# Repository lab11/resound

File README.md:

Resound
==============

This is intended to be a high power version of the 
[Ekho Project](http://github.com/jhester/ekho) to be
used with larger solar powered sensor deployments.

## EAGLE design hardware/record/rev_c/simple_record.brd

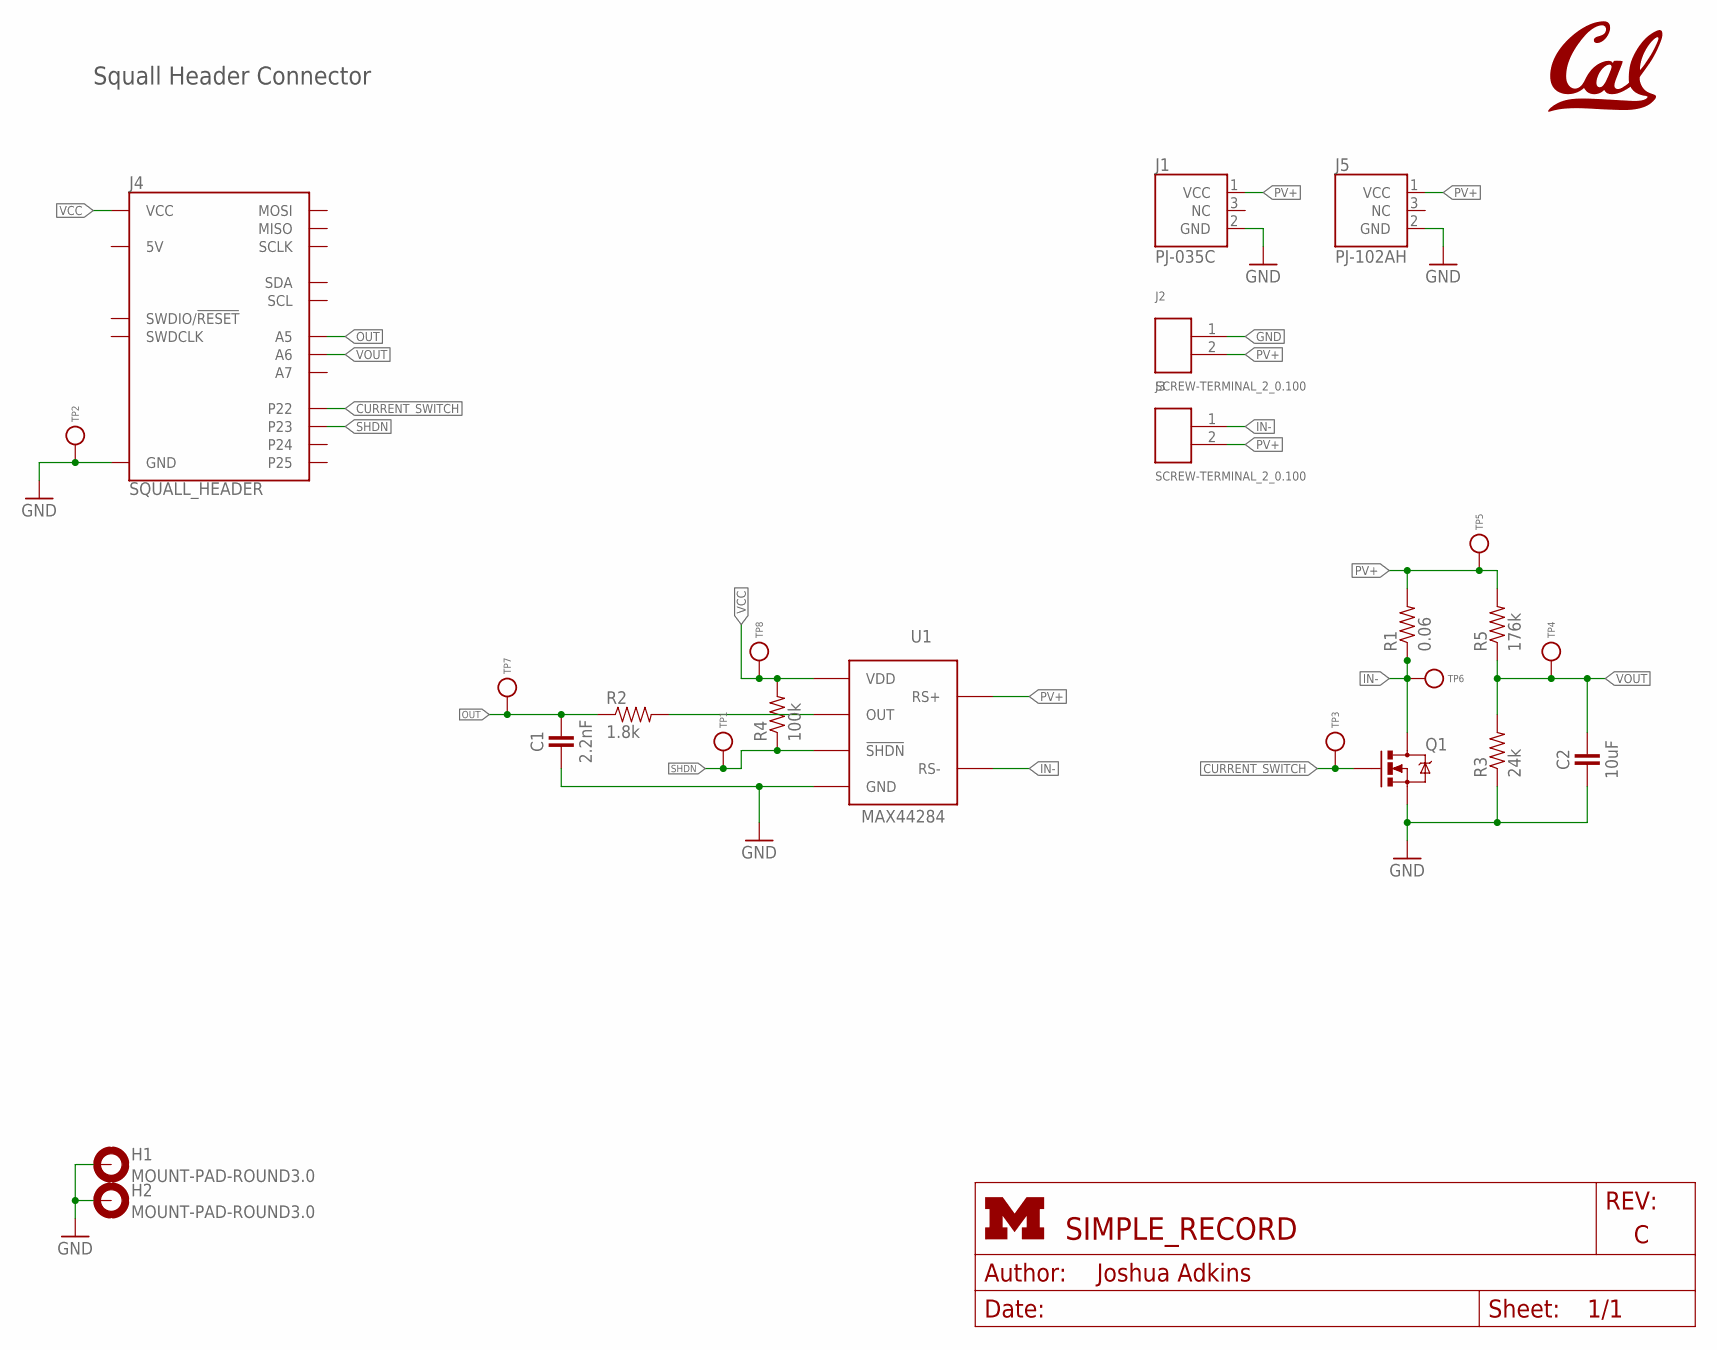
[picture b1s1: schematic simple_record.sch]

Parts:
C1: 2.2nF; 0402_CAP
C2: 10uF; 0603_CAP
H1, H2: MOUNT-PAD-ROUND3.0; 3,0-PAD
J1: PJ-035C
J2, J3: SCREW-TERMINAL_2_0.100; CONN_BLOCK_2
J4: SQUALL_HEADER
J5: PJ-102AH
Q1: MOSFET-NCHANNELSMD; SOT23-3; DIGIKEY DMN3023L-7DICT-ND
R1: 0.06; 0603-RES
R2: 1.8k; 0603-RES
R3: 24k; 0603-RES
R4: 100k; 0603-RES
R5: 176k; 0603-RES
TP1, TP2, TP3, TP4, TP5, TP6, TP7, TP8: TEST_POINT_0.040IN; TESTPOINT_0.040IN
U1: MAX44284; SOT-23-6
U$1: UCB_CAL75MIL; UCB_CAL_75MIL

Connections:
CURRENT_SWITCH: J4.A2 (P22), Q1.1 (G), TP3.TESTPOINT
GND: C1.2, C2.2, H1.B3,0, H2.B3,0, J1.2 (GND), J2.1, J4.A9 (GND), J4.A10 (GND), J5.2 (GND), Q1.2 (S), R3.1, TP2.TESTPOINT, U1.2 (GND)
IN-: J3.1, Q1.3 (D), R1.1, TP6.TESTPOINT, U1.4 (RS-)
unnamed: R2.2, U1.5 (OUT)
OUT: C1.1, J4.B9 (A5), R2.1, TP7.TESTPOINT
PV+: J1.1 (VCC), J2.2, J3.2, J5.1 (VCC), R1.2, R5.2, TP5.TESTPOINT, U1.3 (RS+)
SHDN: J4.A4 (P23), R4.1, TP1.TESTPOINT, U1.6 (!SHDN)
VCC: J4.A1 (VCC), J4.A3 (VCC), R4.2, TP8.TESTPOINT, U1.1 (VDD)
VOUT: C2.1, J4.B7 (A6), R3.2, R5.1, TP4.TESTPOINT

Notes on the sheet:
Squall Header Connector

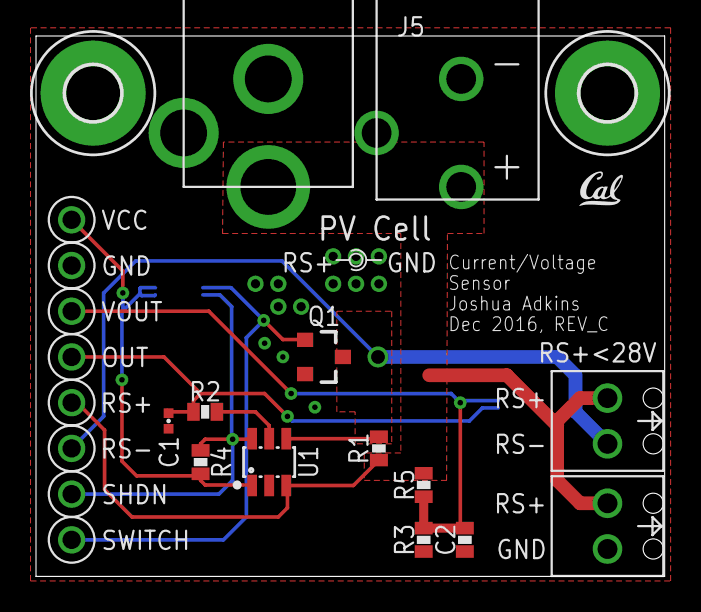
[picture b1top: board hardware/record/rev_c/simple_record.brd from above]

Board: 2 copper layers, 34.9 x 30.0 mm, 25 parts (0 on the bottom side), 9 nets.

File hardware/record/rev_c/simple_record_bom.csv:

# Bill of Materials
# Converted from simple_record_bom.xlsx
# Generated by bom_to_text.py

Qty,Value,Device,Package,Parts,Description,DIGIKEY,MOUSER,NEWARK
1,2.2nF,CAPACITOR,0402_CAP,C1,0402 Capacitor,587-1059-1-ND,,
1,10uF,CAPACITOR0603_CAP,0603_CAP,C2,0603 Capacitor,490-3298-1-ND,,
1,PJ-035C,PJ-035C,PJ-035C,J1,A 1/3.4mm barrel jack part,CP-035C-ND,,
2,SCREW-TERMINAL_2_0.100,SCREW-TERMINAL_2_0.100,CONN_BLOCK_2,"J2, J3",2x 0.100 in screw terminal block,277-1273-ND,651-1725656,71C4107
2,SQUALL_HEADER,SQUALL_HEADER,SQUALL_HEADER,"J4A, J4B",Header for a sensor board on top of the Squall BLE tag board.,H11617CT-ND,,
1,PJ-102AH,PJ-102AH,PJ-102AH,J5,DC Power Jack,CP-102AH-ND,,
1,MOSFET-NCHANNELSMD,MOSFET-NCHANNELSMD,SOT23-3,Q1,Generic NMOS footprint,DMN3023L-7DICT-ND,,
1,0.06,RESISTOR,0603-RES,R1,Resistor,WSLPA-.06CT-ND,,
1,1.8k,RESISTOR,0603-RES,R2,Resistor,311-1.8KGRCT-ND,,
1,24k,RESISTOR,0603-RES,R3,Resistor,RHM24KCFCT-ND,,
1,100k,RESISTOR,0603-RES,R4,Resistor,311-100KGRCT-ND,,
1,176k,RESISTOR,0603-RES,R5,Resistor,311-2094-1-ND,,
7,TEST_POINT_0.040IN,TEST_POINT_0.040IN,TESTPOINT_0.040IN,"TP1, TP2, TP3, TP4, TP5, TP6, TP7",0.040in Test Point,5001K-ND,,
1,MAX44284F,MAX44284F,SOT23-6,U1,,MAX44284FAUT+TCT-ND,,

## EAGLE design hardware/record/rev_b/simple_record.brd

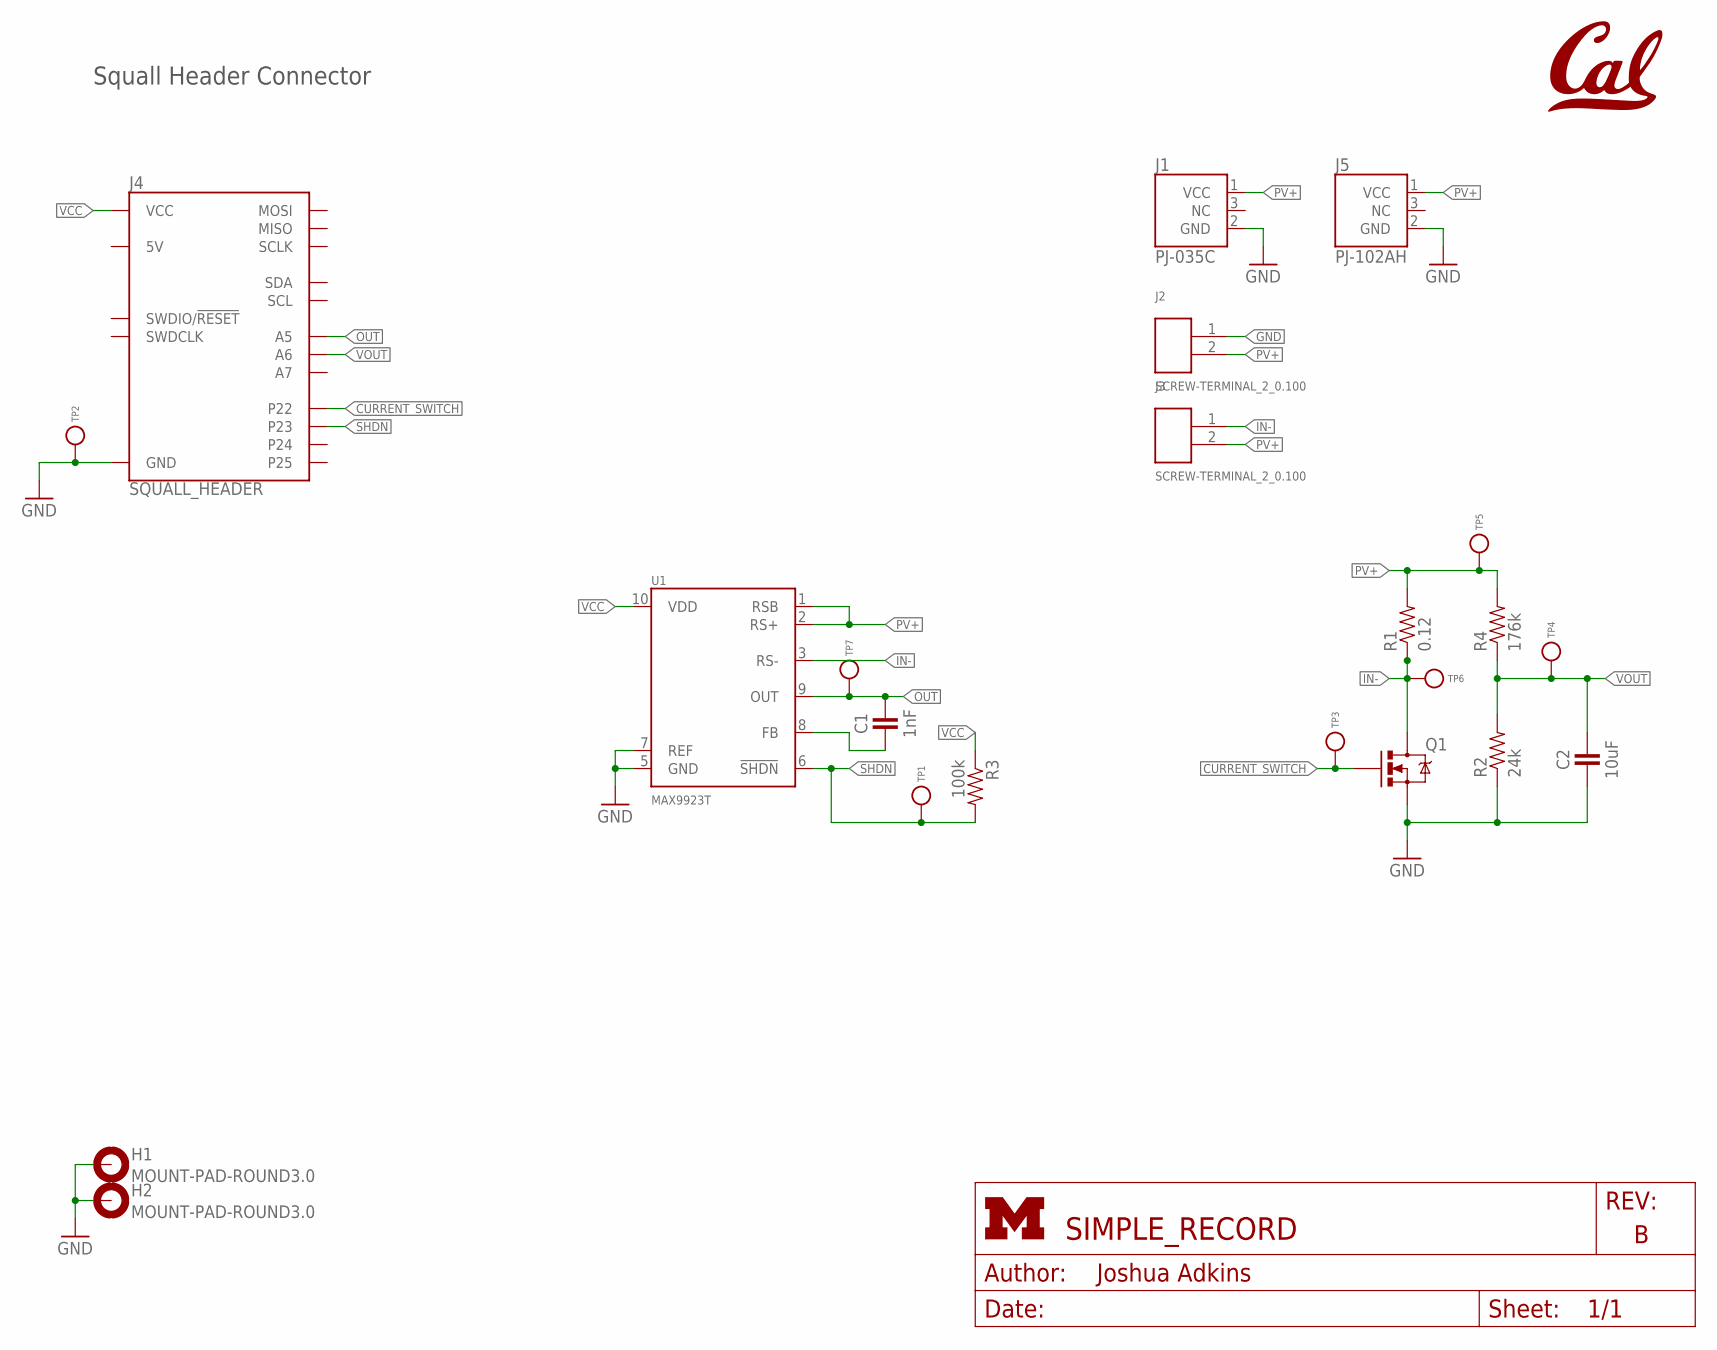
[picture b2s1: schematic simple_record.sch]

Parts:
C1: 1nF; 0402_CAP
C2: 10uF; 0603_CAP
H1, H2: MOUNT-PAD-ROUND3.0; 3,0-PAD
J1: PJ-035C
J2, J3: SCREW-TERMINAL_2_0.100; CONN_BLOCK_2
J4: SQUALL_HEADER
J5: PJ-102AH
Q1: MOSFET-NCHANNELSMD; SOT23-3; DIGIKEY DMN3023L-7DICT-ND
R1: 0.12; 0603-RES
R2: 24k; 0603-RES
R3: 100k; 0603-RES
R4: 176k; 0603-RES
TP1, TP2, TP3, TP4, TP5, TP6, TP7: TEST_POINT_0.040IN; TESTPOINT_0.040IN
U1: MAX9923T; UMAX10; DIGIKEY MAX9923TEUB+TCT-ND
U$1: UCB_CAL75MIL; UCB_CAL_75MIL

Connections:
CURRENT_SWITCH: J4.A2 (P22), Q1.1 (G), TP3.TESTPOINT
GND: C2.2, H1.B3,0, H2.B3,0, J1.2 (GND), J2.1, J4.A9 (GND), J4.A10 (GND), J5.2 (GND), Q1.2 (S), R2.1, TP2.TESTPOINT, U1.5 (GND), U1.7 (REF)
IN-: J3.1, Q1.3 (D), R1.1, TP6.TESTPOINT, U1.3 (RS-)
unnamed: C1.2, U1.8 (FB)
OUT: C1.1, J4.B9 (A5), TP7.TESTPOINT, U1.9 (OUT)
PV+: J1.1 (VCC), J2.2, J3.2, J5.1 (VCC), R1.2, R4.2, TP5.TESTPOINT, U1.1 (RSB), U1.2 (RS+)
SHDN: J4.A4 (P23), R3.2, TP1.TESTPOINT, U1.6 (!SHDN)
VCC: J4.A1 (VCC), J4.A3 (VCC), R3.1, U1.10 (VDD)
VOUT: C2.1, J4.B7 (A6), R2.2, R4.1, TP4.TESTPOINT

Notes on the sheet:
Squall Header Connector

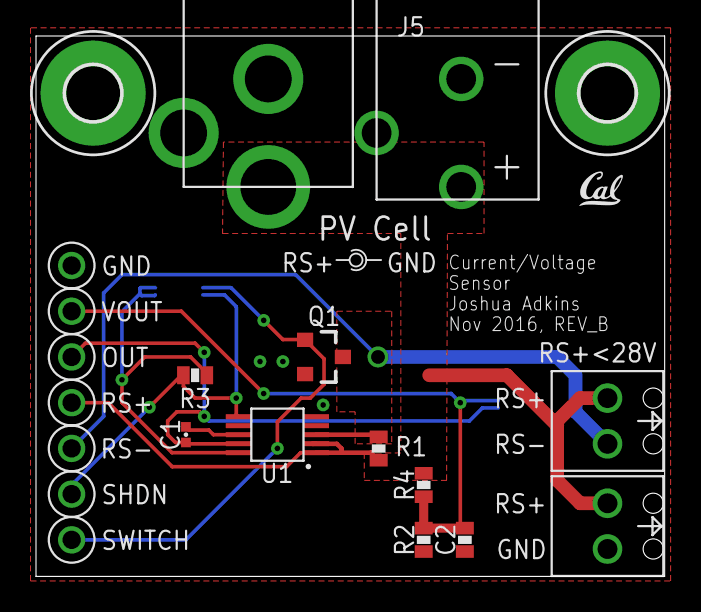
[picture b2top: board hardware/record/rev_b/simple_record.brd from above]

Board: 2 copper layers, 34.9 x 30.0 mm, 23 parts (0 on the bottom side), 9 nets.

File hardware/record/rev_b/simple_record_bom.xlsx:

Qty | Value | Device | Package | Parts | Description | DIGIKEY | MOUSER | NEWARK
1 | 1nF | CAPACITOR | 0402_CAP | C1 | 0402 Capacitor | 490-1303-1-ND
1 | 10uF | CAPACITOR0603_CAP | 0603_CAP | C2 | 0603 Capacitor | 490-3298-1-ND
1 | PJ-035C | PJ-035C | PJ-035C | J1 | A 1/3.4mm barrel jack part | CP-035C-ND
2 | SCREW-TERMINAL_2_0.100 | SCREW-TERMINAL_2_0.100 | CONN_BLOCK_2 | J2, J3 | 2x 0.100 in screw terminal block | 277-1273-ND | 651-1725656 | 71C4107
2 | SQUALL_HEADER | SQUALL_HEADER | SQUALL_HEADER | J4A, J4B | Header for a sensor board on top of the Squall BLE tag board. | H11617CT-ND
1 | PJ-102AH | PJ-102AH | PJ-102AH | J5 | DC Power Jack | CP-102AH-ND
1 | MOSFET-NCHANNELSMD | MOSFET-NCHANNELSMD | SOT23-3 | Q1 | Generic NMOS footprint | DMN3023L-7DICT-ND
1 | 0.12 | RESISTOR | 0603-RES | R1 | Resistor | RHM1241CT-ND
1 | 24k | RESISTOR | 0603-RES | R2 | Resistor | RHM24KCFCT-ND
1 | 100k | RESISTOR | 0603-RES | R3 | Resistor | 311-100KGRCT-ND
1 | 176k | RESISTOR | 0603-RES | R4 | Resistor | 311-2094-1-ND
7 | TEST_POINT_0.040IN | TEST_POINT_0.040IN | TESTPOINT_0.040IN | TP1, TP2, TP3, TP4, TP5, TP6, TP7 | 0.040in Test Point | 5001K-ND
1 | MAX9923T | MAX9923T | UMAX10 | U1 | The MAX9922/MAX9923 ultra-precision, high-side current- | MAX9923TEUB+TCT-ND

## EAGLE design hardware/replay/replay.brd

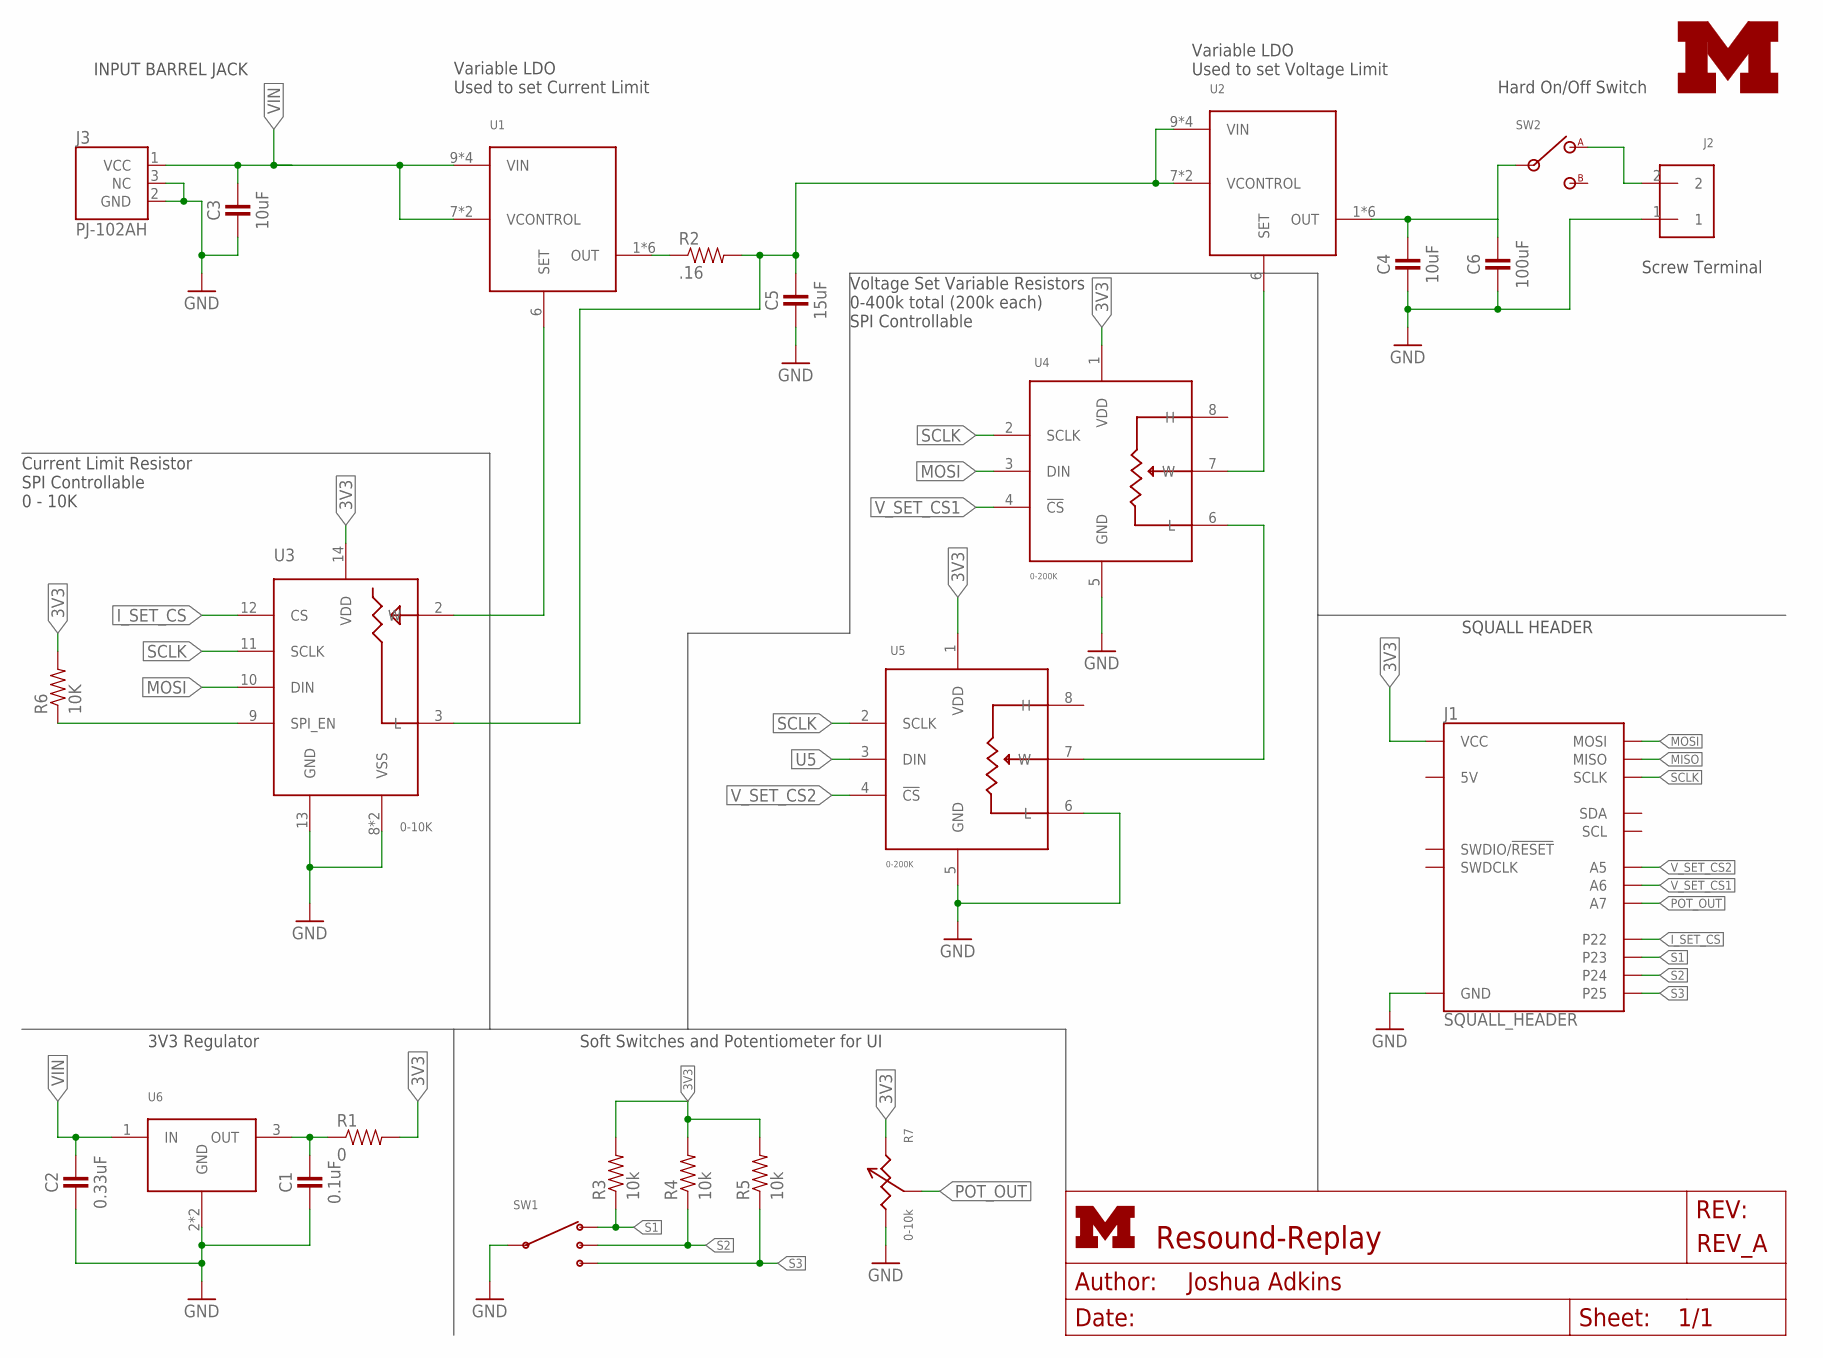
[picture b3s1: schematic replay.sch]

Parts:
C1: 0.1uF; 0603_CAP
C2: 0.33uF; 0603_CAP
C3, C4: 10uF; 0603_CAP
C5: 15uF; 0603_CAP
C6: 100uF; 0603_CAP
J1: SQUALL_HEADER
J2: SCREW_TERMINAL; PHEONIX-1935161
J3: PJ-102AH
LOGO1: UMICH_SOLID_SMALL; UMICH_SOLID_75MIL
R1: 0; 0603-RES
R2: .16; R2512
R3, R4, R5: 10k; 0603-RES
R6: 10K; 0603-RES
R7: 0-10k; 3310C
SW1: OS103011
SW2: 500ASSP
U1, U2: LT3083; DFN-12/4MM
U3: 0-10K; TQFN-16/3MM
U4, U5: 0-200K; TDFN-8/3MM
U6: UA78MXX; SOT-223

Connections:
3V3: J1.A1 (VCC), J1.A3 (VCC), R1.2, R3.2, R4.2, R5.2, R6.2, R7.1, U3.14 (VDD), U4.1 (VDD), U5.1 (VDD)
GND: C1.2, C2.2, C3.2, C4.2, C5.2, C6.2, J1.A9 (GND), J1.A10 (GND), J2.1, J3.2 (GND), J3.3 (NC), R7.3, SW1.2 (C), U3.8 (VSS), U3.13 (GND), U3.16 (VSS), U4.5 (GND), U5.5 (GND), U5.6 (L), U6.2 (GND), U6.4 (GND)
I_SET_CS: J1.A2 (P22), U3.12 (CS)
MISO: J1.B8 (MISO)
MOSI: J1.B6 (MOSI), U3.10 (DIN), U4.3 (DIN)
unnamed: U1.6 (SET), U3.2 (W)
unnamed: U2.6 (SET), U4.7 (W)
unnamed: U4.6 (L), U5.7 (W)
unnamed: C1.1, R1.1, U6.3 (OUT)
unnamed: R6.1, U3.9 (SPI_EN)
OUT: C4.1, C6.1, SW2.2, U2.1 (OUT), U2.2 (OUT), U2.3 (OUT), U2.4 (OUT), U2.5 (OUT), U2.13 (OUT)
OUT1: R2.1, U1.1 (OUT), U1.2 (OUT), U1.3 (OUT), U1.4 (OUT), U1.5 (OUT), U1.13 (OUT)
OUTS: J2.2, SW2.1
POT_OUT: J1.B5 (A7), R7.2
S1: J1.A4 (P23), R3.1, SW1.4 (3)
S2: J1.A6 (P24), R4.1, SW1.3 (2)
S3: J1.A8 (P25), R5.1, SW1.1
SCLK: J1.B10 (SCLK), U3.11 (SCLK), U4.2 (SCLK), U5.2 (SCLK)
U5: U5.3 (DIN)
VIN: C2.1, C3.1, J3.1 (VCC), U1.7 (VCONTROL), U1.8 (VCONTROL), U1.9 (VIN), U1.10 (VIN), U1.11 (VIN), U1.12 (VIN), U6.1 (IN)
VIN2: C5.1, R2.2, U2.7 (VCONTROL), U2.8 (VCONTROL), U2.9 (VIN), U2.10 (VIN), U2.11 (VIN), U2.12 (VIN), U3.3 (L)
V_SET_CS1: J1.B7 (A6), U4.4 (!CS)
V_SET_CS2: J1.B9 (A5), U5.4 (!CS)

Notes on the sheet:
3V3 Regulator
Soft Switches and Potentiometer for UI
INPUT BARREL JACK
Current Limit Resistor SPI Controllable 0 - 10K
Variable LDO Used to set Current Limit
SQUALL HEADER
Variable LDO Used to set Voltage Limit
Hard On/Off Switch
Screw Terminal
Voltage Set Variable Resistors 0-400k total (200k each) SPI Controllable

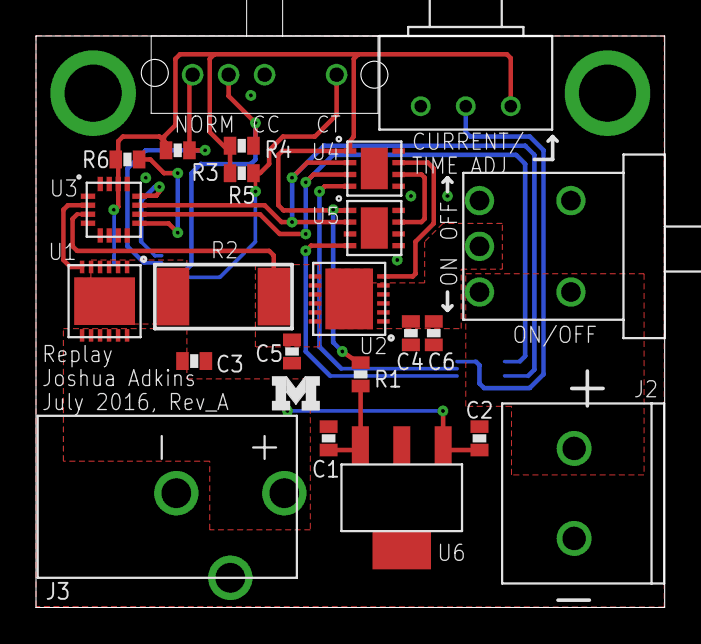
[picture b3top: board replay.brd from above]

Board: 2 copper layers, 34.9 x 31.8 mm, 25 parts (0 on the bottom side), 21 nets.

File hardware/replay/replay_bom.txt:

# Bill of Materials
# Converted from replay_bom.xlsx
# Generated by bom_to_text.py

Part   Value              Device             Package            Description                                                    DIGIKEY
C1     0.1uF              CAPACITOR0603_CAP  0603_CAP           0402 Capacitor                                                 
C2     0.33uF             CAPACITOR0603_CAP  0603_CAP           0402 Capacitor                                                 
C3     10uF               CAPACITOR0603_CAP  0603_CAP           0402 Capacitor                                                 
C4     10uF               CAPACITOR0603_CAP  0603_CAP           0402 Capacitor                                                 
C5     15uF               CAPACITOR0603_CAP  0603_CAP           0402 Capacitor                                                 
C6     100uF              CAPACITOR0603_CAP  0603_CAP           0402 Capacitor                                                 
J1     SQUALL_HEADER      SQUALL_HEADER      SQUALL_HEADER      Header for a sensor board on top of the Squall BLE tag board.  H11617CT-ND
J2     SCREW_TERMINAL     SCREW_TERMINAL     PHEONIX-1935161    PCB terminal block 5mm                                         277-1667-ND
J3     PJ-102AH           PJ-102AH           PJ-102AH           DC Power Jack                                                  CP-102AH-ND
LOGO1  UMICH_SOLID_SMALL  UMICH_SOLID_SMALL  UMICH_SOLID_75MIL                                                                 
R1     0                  RESISTOR           0603-RES           Resistor                                                       
R2     0.16               RESISTOR2512       R2512              Resistor                                                       
R3     10k                RESISTOR           0603-RES           Resistor                                                       
R4     10k                RESISTOR           0603-RES           Resistor                                                       
R5     10k                RESISTOR           0603-RES           Resistor                                                       
R6     10K                RESISTOR           0603-RES           Resistor                                                       
R7     0-10k              POT3310C           3310C              Potentiometer                                                  3310C-125-103L-ND
SW1    OS103011           OS103011           OS103011           SP3T right angle switch                                        CKN9561-ND
SW2    500ASSP            500ASSP            500ASSP            High current slide switch                                      EG2483-ND
U1     LT3083             LT3083             DFN-12/4MM         3A resistor programmable LDO                                   LT3083IDF#PBF-ND
U2     LT3083             LT3083             DFN-12/4MM         3A resistor programmable LDO                                   LT3083IDF#PBF-ND
U3     0-10K              MAX5483            TQFN-16/3MM        SPI Programmable Rheostat                                      MAX5483ETE+-ND
U4     0-200K             MAX5424            TDFN-8/3MM         Variable POT 256 Tap                                           MAX5424ETA+TCT-ND
U5     0-200K             MAX5424            TDFN-8/3MM         Variable POT 256 Tap                                           MAX5424ETA+TCT-ND
U6                        UA78MXX            SOT-223            Wide voltage input range LDO, 500ma, vin=5-25v                 296-13424-1-ND

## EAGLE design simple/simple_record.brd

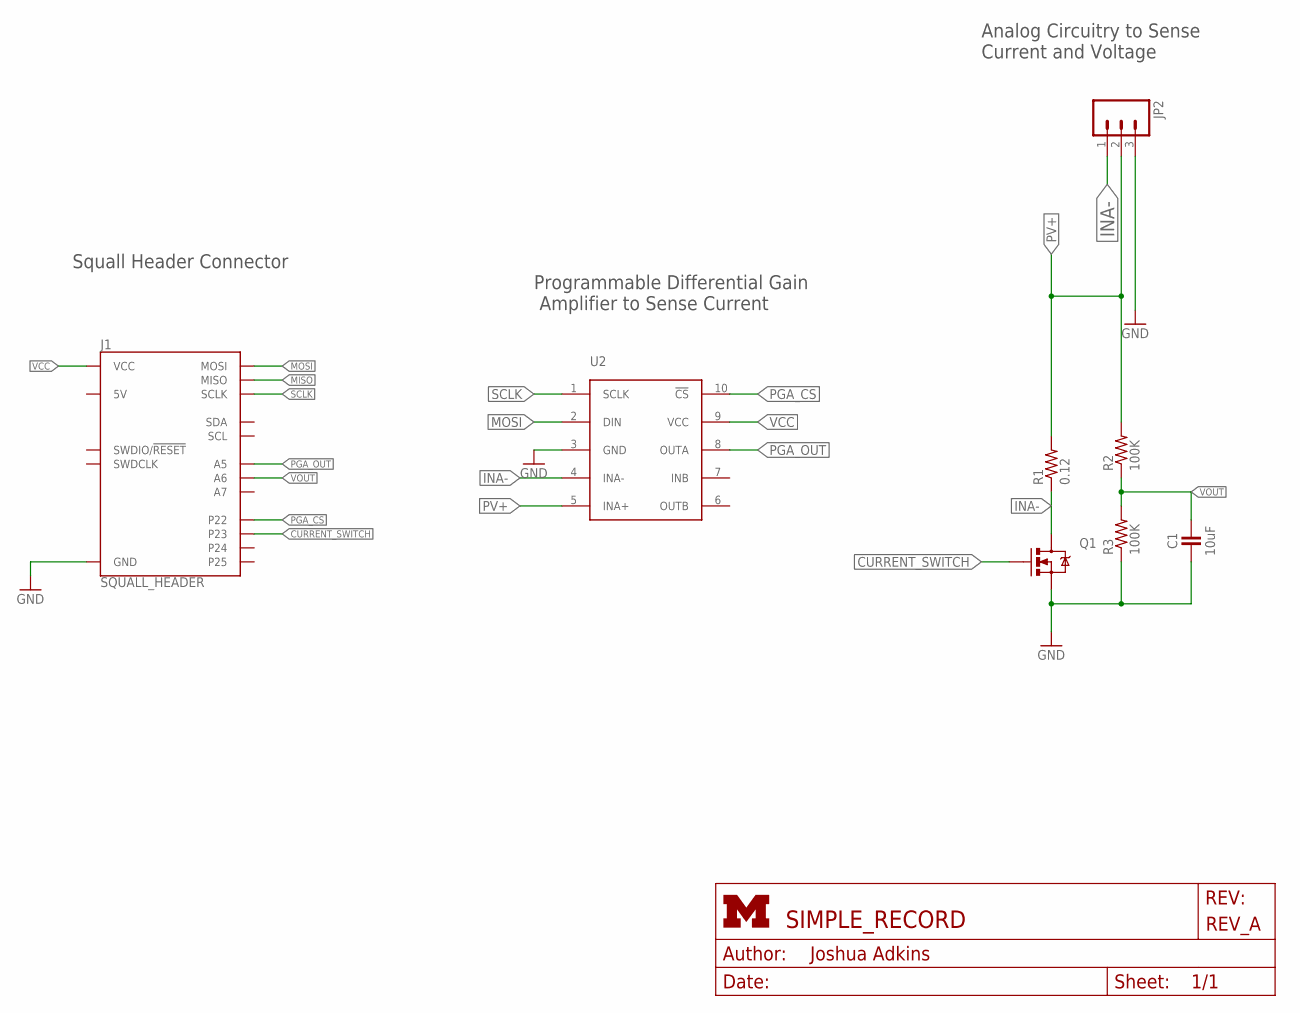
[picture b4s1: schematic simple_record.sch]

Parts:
C1: 10uF; 0402_CAP
J1: SQUALL_HEADER
JP2: M03PTH; 1X03
Q1: MOSFET-NCHANNELSMD; SOT23-3
R1: 0.12; 0603-RES
R2, R3: 100K; 0603-RES
U2: MAX9939; UMAX10

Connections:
CURRENT_SWITCH: J1.A4 (P23), Q1.1 (G)
GND: C1.2, J1.A9 (GND), J1.A10 (GND), JP2.3, Q1.2 (S), R3.1, U2.3 (GND)
INA-: JP2.1, Q1.3 (D), R1.1, U2.4 (INA-)
MISO: J1.B8 (MISO)
MOSI: J1.B6 (MOSI), U2.2 (DIN)
PGA_CS: J1.A2 (P22), U2.10 (!CS)
PGA_OUT: J1.B9 (A5), U2.8 (OUTA)
PV+: JP2.2, R1.2, R2.2, U2.5 (INA+)
SCLK: J1.B10 (SCLK), U2.1 (SCLK)
VCC: J1.A1 (VCC), J1.A3 (VCC), U2.9 (VCC)
VOUT: C1.1, J1.B7 (A6), R2.1, R3.2

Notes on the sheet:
Squall Header Connector
Programmable Differential Gain Amplifier to Sense Current
Analog Circuitry to Sense Current and Voltage

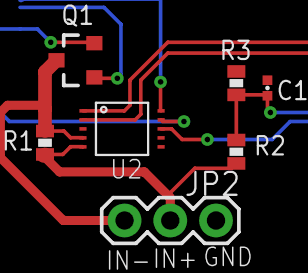
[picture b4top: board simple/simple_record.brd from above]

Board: 2 copper layers, 8 parts (0 on the bottom side), 10 nets.

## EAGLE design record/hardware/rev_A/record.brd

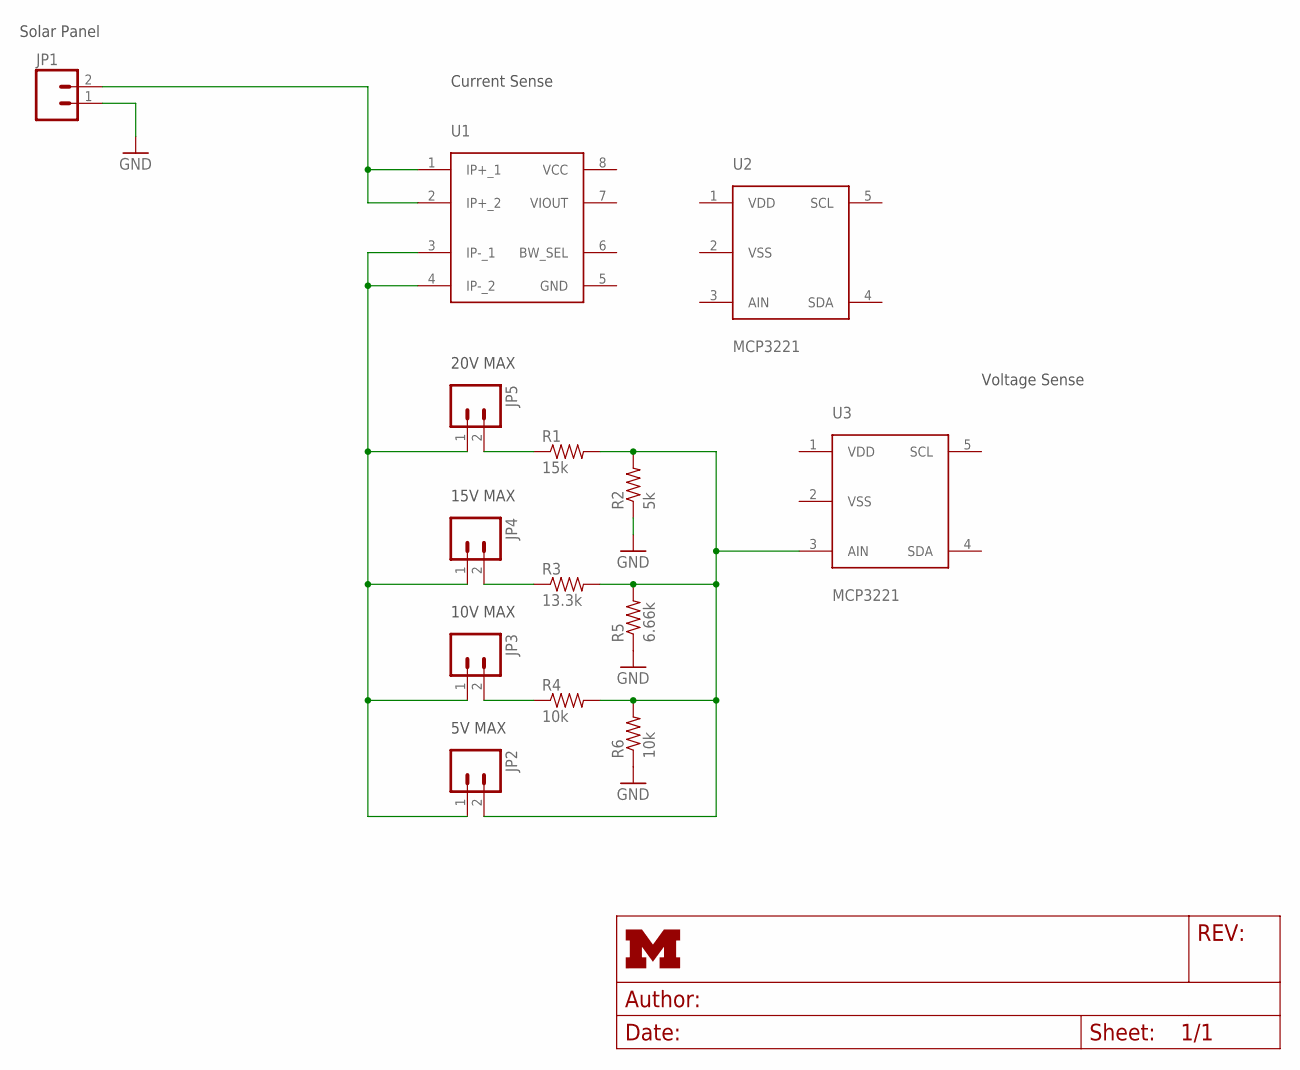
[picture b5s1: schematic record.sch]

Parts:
JP1, JP2, JP3, JP4, JP5: M02PTH; 1X02
R1: 15k; 0603-RES
R2: 5k; 0603-RES
R3: 13.3k; 0603-RES
R4, R6: 10k; 0603-RES
R5: 6.66k; 0603-RES
U1: ACS723; SOIC-8
U2, U3: MCP3221; SOT-23-5

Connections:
GND: JP1.1, R2.1, R5.1, R6.1
unnamed: JP1.2, U1.1 (IP+_1), U1.2 (IP+_2)
unnamed: JP2.1, JP3.1, JP4.1, JP5.1, U1.3 (IP-_1), U1.4 (IP-_2)
unnamed: JP5.2, R1.1
unnamed: JP2.2, R1.2, R2.2, R3.2, R4.2, R5.2, R6.2, U3.3 (AIN)
unnamed: JP4.2, R3.1
unnamed: JP3.2, R4.1

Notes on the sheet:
Solar Panel
Current Sense
Voltage Sense
20V MAX
15V MAX
10V MAX
5V MAX

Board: 2 copper layers, 14 parts (0 on the bottom side), 7 nets, no tracks yet.

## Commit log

2016-06-02 Readme commit
2016-06-03 added the start of two board files and the gitignore
2016-06-09 added a squall shield that can do solar panel current sensing
2016-06-09 finalized title and some layout details
2016-06-10 ran drc on the board
2016-06-10 added the files being sent to fab
2016-06-30 moved some stuff around
2016-07-01 first pass at the replay board layout
2016-07-07 board layed out with switches
2016-07-08 updated parts on the board and started making a case
2016-07-08 cleaned up schematic and changed screw terminal
2016-07-09 added the shipped version of replay
2016-11-08 moved some things and designed new opamp circuit
2016-11-09 updated rev_b of the board to new chip
2016-11-09 renumbered parts
2016-11-11 Revert "renumbered parts"
    This reverts commit aba0891c6fa3a8957b5f6f1ce6d6696c13dad33f.
    Something wonky happened there. I sure hope that commit message is
    accurate and nothing else was changed...
2016-11-11 properly renumber parts
2016-11-11 beautify
2016-11-11 updated board and bom
2016-11-11 updates
    - added second barrel jack
    - resized to be same size as logger board
    - compressed test points to be 0.1" header friendly
2016-11-11 better ground, moved barrel jacks farther out
2016-11-11 add built zips
2016-12-02 added a hoepfully not wrong version of this board.
    the amplifier on rev_B was not made to do that.
    It had too high of a minimum CMRR
    I need CMRR down to 0 due to the ground short
    measuring short circuit current of the panel
2016-12-04 Cleaned up some silkscreen, lined up VCC TP
2016-12-04 whats with the weird put the testpoints over the
    signals so it looks all weird thing? Why not make TPs stand out like
    flags? I don't get it.
2016-12-05 changed the revision in the sch
2016-12-05 added more gnd vias
2016-12-05 added production files

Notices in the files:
parts and their libraries:
SparkFun-Aesthetics: Licensing: CC v3.0 Share-Alike You are welcome to use this library for commercial purposes.
